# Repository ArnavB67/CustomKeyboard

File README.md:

# CustomKeyboard

In a month or two I am going to start with college, since I chose my major to be Electronics I wanted to get experience with making electronic projects, hence i decided to learn pcb designing and 3d modelling necessary parts. As my first electronic project i decided to make a simple custom mechanical keyboard with no rgb or bluetooth or any display, just typing.

The whole journey making this taught me how a keyboard works, how do we design a pcb,the difference between a pcb and a schematic, fundamentals for onshape 3d modelling, Initially i struggled with grid system in kicad and placing pcb switches, and making the case.

this project was a simple keyboard with only diodes switches and a raspberry pi pico, i didnt add anything like rgb,displays,bluetooth or rotatory encoder.

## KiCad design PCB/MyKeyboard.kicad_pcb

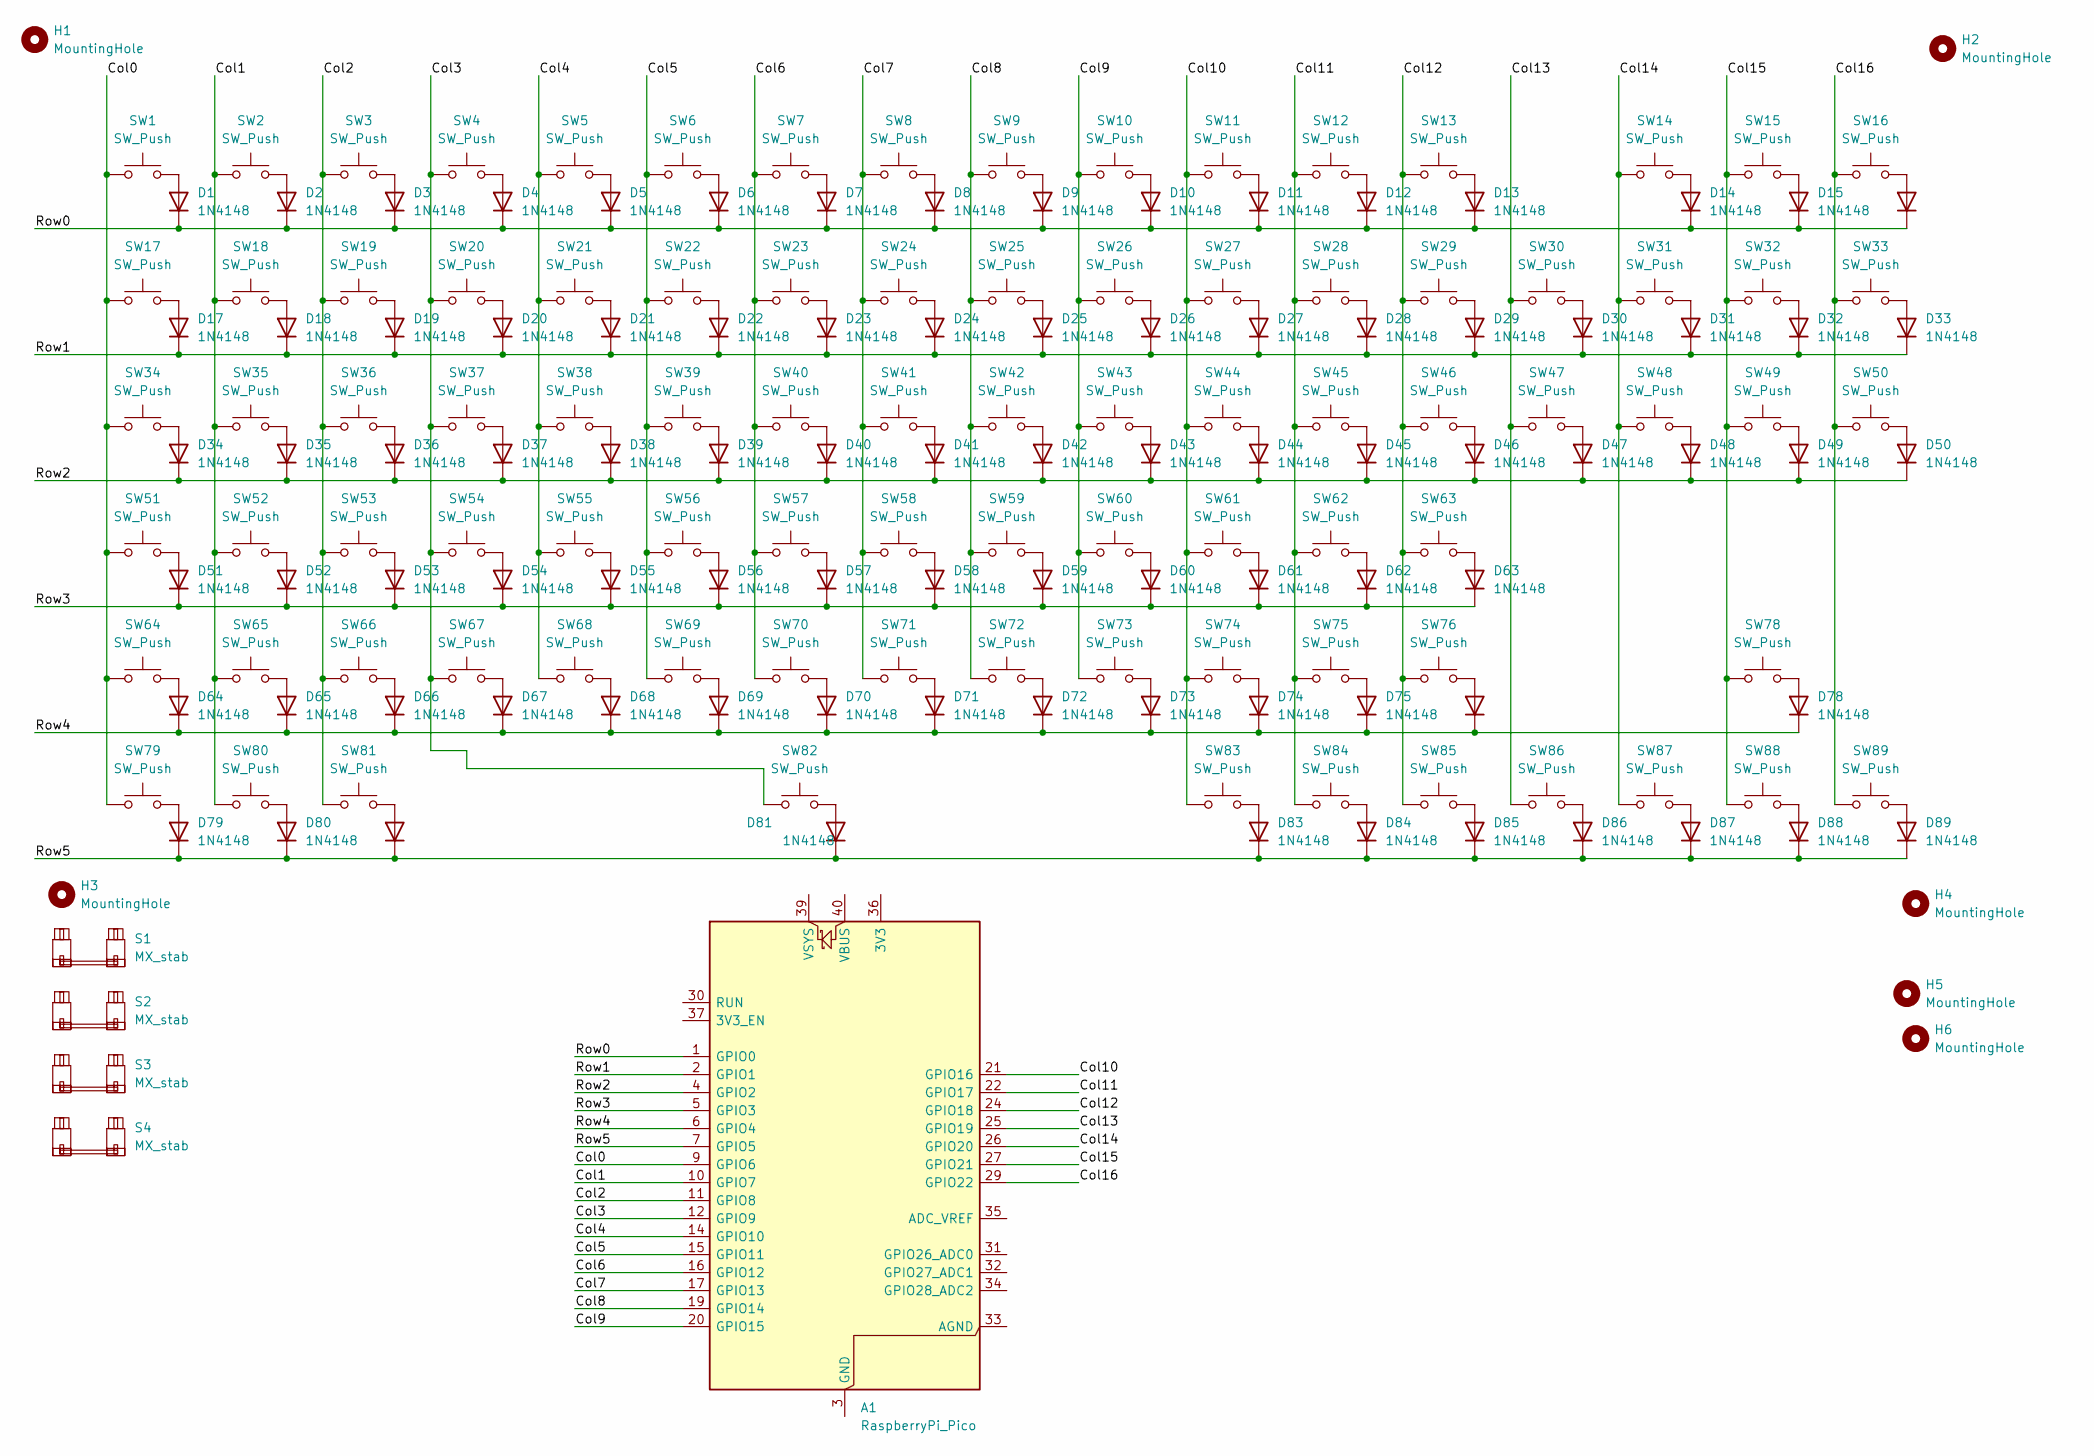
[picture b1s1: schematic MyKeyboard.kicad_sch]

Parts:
A1: RaspberryPi_Pico; RaspberryPi_Pico_Common_THT
D1, D2, D3, D4, D5, D6, D7, D8, D9, D10, D11, D12, D13, D14, D15, D16, D17, D18, D19, D20, D21, D22, D23, D24, D25, D26, D27, D28, D29, D30, D31, D32, D33, D34, D35, D36, D37, D38, D39, D40, D41, D42, D43, D44, D45, D46, D47, D48, D49, D50, D51, D52, D53, D54, D55, D56, D57, D58, D59, D60, D61, D62, D63, D64, D65, D66, D67, D68, D69, D70, D71, D72, D73, D74, D75, D76, D78, D79, D80, D81, D82, D83, D84, D85, D86, D87, D88, D89: 1N4148; D_DO-35_SOD27_P7.62mm_Horizontal
H1, H2, H3, H4, H5, H6: MountingHole; MountingHole_2.2mm_M2
S1: MX_stab; STAB_MX_6.25u
S2, S3: MX_stab; STAB_MX_2u
S4: MX_stab; STAB_MX_ISO
SW1, SW2, SW3, SW4, SW5, SW6, SW7, SW8, SW9, SW10, SW11, SW12, SW13, SW14, SW15, SW16, SW17, SW18, SW19, SW20, SW21, SW22, SW23, SW24, SW25, SW26, SW27, SW28, SW29, SW30, SW31, SW32, SW33, SW34, SW35, SW36, SW37, SW38, SW39, SW40, SW41, SW42, SW43, SW44, SW45, SW46, SW47, SW48, SW49, SW50, SW51, SW52, SW53, SW54, SW55, SW56, SW57, SW58, SW59, SW60, SW61, SW62, SW63, SW64, SW65, SW66, SW67, SW68, SW69, SW70, SW71, SW72, SW73, SW74, SW75, SW76, SW78, SW79, SW80, SW81, SW82, SW83, SW84, SW85, SW86, SW87, SW88, SW89: SW_Push; SW_MX_1u

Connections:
/Col0: A1.9 (GPIO6), SW1.1, SW17.1, SW34.1, SW51.1, SW64.1, SW79.1
/Col1: A1.10 (GPIO7), SW2.1, SW18.1, SW35.1, SW52.1, SW65.1, SW80.1
/Col2: A1.11 (GPIO8), SW3.1, SW19.1, SW36.1, SW53.1, SW66.1, SW81.1
/Col3: A1.12 (GPIO9), SW4.1, SW20.1, SW37.1, SW54.1, SW67.1, SW82.1
/Col4: A1.14 (GPIO10), SW5.1, SW21.1, SW38.1, SW55.1, SW68.1
/Col5: A1.15 (GPIO11), SW6.1, SW22.1, SW39.1, SW56.1, SW69.1
/Col6: A1.16 (GPIO12), SW7.1, SW23.1, SW40.1, SW57.1, SW70.1
/Col7: A1.17 (GPIO13), SW8.1, SW24.1, SW41.1, SW58.1, SW71.1
/Col8: A1.19 (GPIO14), SW9.1, SW25.1, SW42.1, SW59.1, SW72.1
/Col9: A1.20 (GPIO15), SW10.1, SW26.1, SW43.1, SW60.1, SW73.1
/Col10: A1.21 (GPIO16), SW11.1, SW27.1, SW44.1, SW61.1, SW74.1, SW83.1
/Col11: A1.22 (GPIO17), SW12.1, SW28.1, SW45.1, SW62.1, SW75.1, SW84.1
/Col12: A1.24 (GPIO18), SW13.1, SW29.1, SW46.1, SW63.1, SW76.1, SW85.1
/Col13: A1.25 (GPIO19), SW30.1, SW47.1, SW86.1
/Col14: A1.26 (GPIO20), SW14.1, SW31.1, SW48.1, SW87.1
/Col15: A1.27 (GPIO21), SW15.1, SW32.1, SW49.1, SW78.1, SW88.1
/Col16: A1.29 (GPIO22), SW16.1, SW33.1, SW50.1, SW89.1
/Row0: A1.1 (GPIO0), D1.1 (K), D2.1 (K), D3.1 (K), D4.1 (K), D5.1 (K), D6.1 (K), D7.1 (K), D8.1 (K), D9.1 (K), D10.1 (K), D11.1 (K), D12.1 (K), D13.1 (K), D14.1 (K), D15.1 (K), D16.1 (K)
/Row1: A1.2 (GPIO1), D17.1 (K), D18.1 (K), D19.1 (K), D20.1 (K), D21.1 (K), D22.1 (K), D23.1 (K), D24.1 (K), D25.1 (K), D26.1 (K), D27.1 (K), D28.1 (K), D29.1 (K), D30.1 (K), D31.1 (K), D32.1 (K), D33.1 (K)
/Row2: A1.4 (GPIO2), D34.1 (K), D35.1 (K), D36.1 (K), D37.1 (K), D38.1 (K), D39.1 (K), D40.1 (K), D41.1 (K), D42.1 (K), D43.1 (K), D44.1 (K), D45.1 (K), D46.1 (K), D47.1 (K), D48.1 (K), D49.1 (K), D50.1 (K)
/Row3: A1.5 (GPIO3), D51.1 (K), D52.1 (K), D53.1 (K), D54.1 (K), D55.1 (K), D56.1 (K), D57.1 (K), D58.1 (K), D59.1 (K), D60.1 (K), D61.1 (K), D62.1 (K), D63.1 (K)
/Row4: A1.6 (GPIO4), D64.1 (K), D65.1 (K), D66.1 (K), D67.1 (K), D68.1 (K), D69.1 (K), D70.1 (K), D71.1 (K), D72.1 (K), D73.1 (K), D74.1 (K), D75.1 (K), D76.1 (K), D78.1 (K)
/Row5: A1.7 (GPIO5), D79.1 (K), D80.1 (K), D81.1 (K), D82.1 (K), D83.1 (K), D84.1 (K), D85.1 (K), D86.1 (K), D87.1 (K), D88.1 (K), D89.1 (K)
unnamed: A1.3 (GND), A1.8 (GND), A1.13 (GND), A1.18 (GND), A1.23 (GND), A1.28 (GND), A1.38 (GND)
unnamed: D1.2 (A), SW1.2
unnamed: D2.2 (A), SW2.2
unnamed: D3.2 (A), SW3.2
unnamed: D4.2 (A), SW4.2
unnamed: D5.2 (A), SW5.2
unnamed: D6.2 (A), SW6.2
unnamed: D7.2 (A), SW7.2
unnamed: D8.2 (A), SW8.2
unnamed: D9.2 (A), SW9.2
unnamed: D10.2 (A), SW10.2
unnamed: D11.2 (A), SW11.2
unnamed: D12.2 (A), SW12.2
unnamed: D13.2 (A), SW13.2
unnamed: D14.2 (A), SW14.2
unnamed: D15.2 (A), SW15.2
unnamed: D16.2 (A), SW16.2
unnamed: D17.2 (A), SW17.2
unnamed: D18.2 (A), SW18.2
unnamed: D19.2 (A), SW19.2
unnamed: D20.2 (A), SW20.2
unnamed: D21.2 (A), SW21.2
unnamed: D22.2 (A), SW22.2
unnamed: D23.2 (A), SW23.2
unnamed: D24.2 (A), SW24.2
unnamed: D25.2 (A), SW25.2
unnamed: D26.2 (A), SW26.2
unnamed: D27.2 (A), SW27.2
unnamed: D28.2 (A), SW28.2
unnamed: D29.2 (A), SW29.2
unnamed: D30.2 (A), SW30.2
unnamed: D31.2 (A), SW31.2
unnamed: D32.2 (A), SW32.2
unnamed: D33.2 (A), SW33.2
unnamed: D34.2 (A), SW34.2
unnamed: D35.2 (A), SW35.2
unnamed: D36.2 (A), SW36.2
unnamed: D37.2 (A), SW37.2
unnamed: D38.2 (A), SW38.2
unnamed: D39.2 (A), SW39.2
unnamed: D40.2 (A), SW40.2
unnamed: D41.2 (A), SW41.2
unnamed: D42.2 (A), SW42.2
unnamed: D43.2 (A), SW43.2
unnamed: D44.2 (A), SW44.2
unnamed: D45.2 (A), SW45.2
unnamed: D46.2 (A), SW46.2
unnamed: D47.2 (A), SW47.2
unnamed: D48.2 (A), SW48.2
unnamed: D49.2 (A), SW49.2
unnamed: D50.2 (A), SW50.2
unnamed: D51.2 (A), SW51.2
unnamed: D52.2 (A), SW52.2
unnamed: D53.2 (A), SW53.2
unnamed: D54.2 (A), SW54.2
unnamed: D55.2 (A), SW55.2
unnamed: D56.2 (A), SW56.2
unnamed: D57.2 (A), SW57.2
unnamed: D58.2 (A), SW58.2
unnamed: D59.2 (A), SW59.2
unnamed: D60.2 (A), SW60.2
unnamed: D61.2 (A), SW61.2
unnamed: D62.2 (A), SW62.2
unnamed: D63.2 (A), SW63.2
unnamed: D64.2 (A), SW64.2
unnamed: D65.2 (A), SW65.2
unnamed: D66.2 (A), SW66.2
unnamed: D67.2 (A), SW67.2
unnamed: D68.2 (A), SW68.2
unnamed: D69.2 (A), SW69.2
unnamed: D70.2 (A), SW70.2
unnamed: D71.2 (A), SW71.2
unnamed: D72.2 (A), SW72.2
unnamed: D73.2 (A), SW73.2
unnamed: D74.2 (A), SW74.2
unnamed: D75.2 (A), SW75.2
unnamed: D76.2 (A), SW76.2
unnamed: D78.2 (A), SW78.2
unnamed: D79.2 (A), SW79.2
unnamed: D80.2 (A), SW80.2
unnamed: D81.2 (A), SW81.2
unnamed: D82.2 (A), SW82.2
unnamed: D83.2 (A), SW83.2
unnamed: D84.2 (A), SW84.2
unnamed: D85.2 (A), SW85.2
unnamed: D86.2 (A), SW86.2
unnamed: D87.2 (A), SW87.2
unnamed: D88.2 (A), SW88.2
unnamed: D89.2 (A), SW89.2

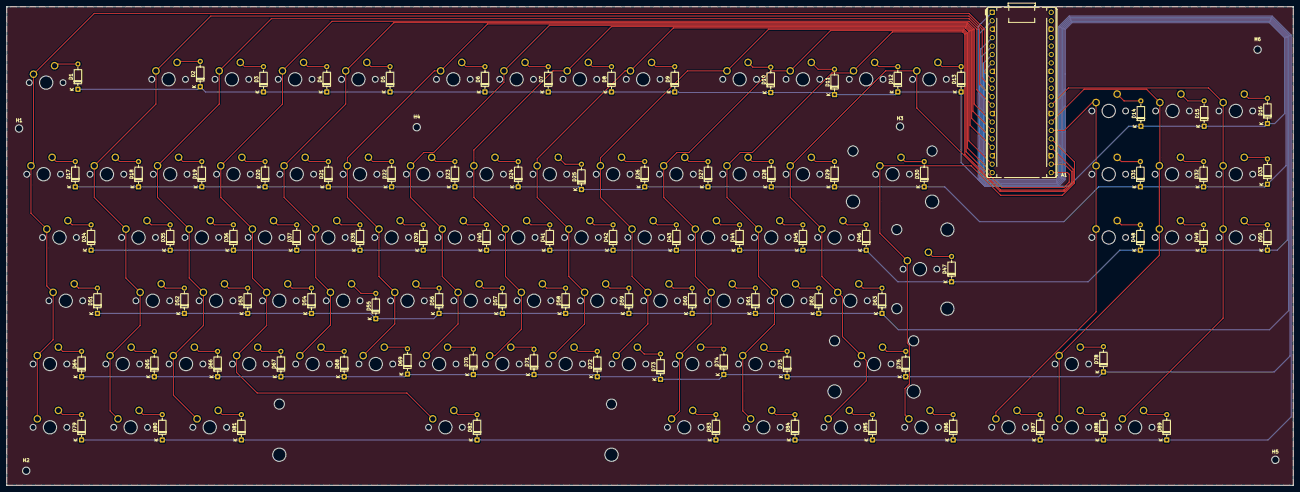
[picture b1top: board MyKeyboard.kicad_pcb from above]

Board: 2 copper layers, 387.3 x 144.1 mm, 187 parts (0 on the bottom side), 112 nets.

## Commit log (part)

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2026-06-27 Add initial entry for Day 1 journal
2026-06-27 Update Day1 journal with Kicad project details
    Documented the process of creating a project in Kicad, including research on schematics, keybinds, and component placement.
2026-06-28 Add Day 2 journal entry on PCB designing
    Documented the process of PCB designing, including key placement and routing traces.
2026-06-29 Add Day 3 journal entry on case building
    Documented the progress of building the case, including steps taken and images of the work.
2026-06-30 Create PCB
2026-06-30 Update README with project details and images
    Added project description and images for CustomKeyboard.
